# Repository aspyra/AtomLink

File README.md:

# AtomLink
 M5Stack Atom Lite based Bluetooth & infrared converter for use in Lego creations. Multiple software options to suit various needs.

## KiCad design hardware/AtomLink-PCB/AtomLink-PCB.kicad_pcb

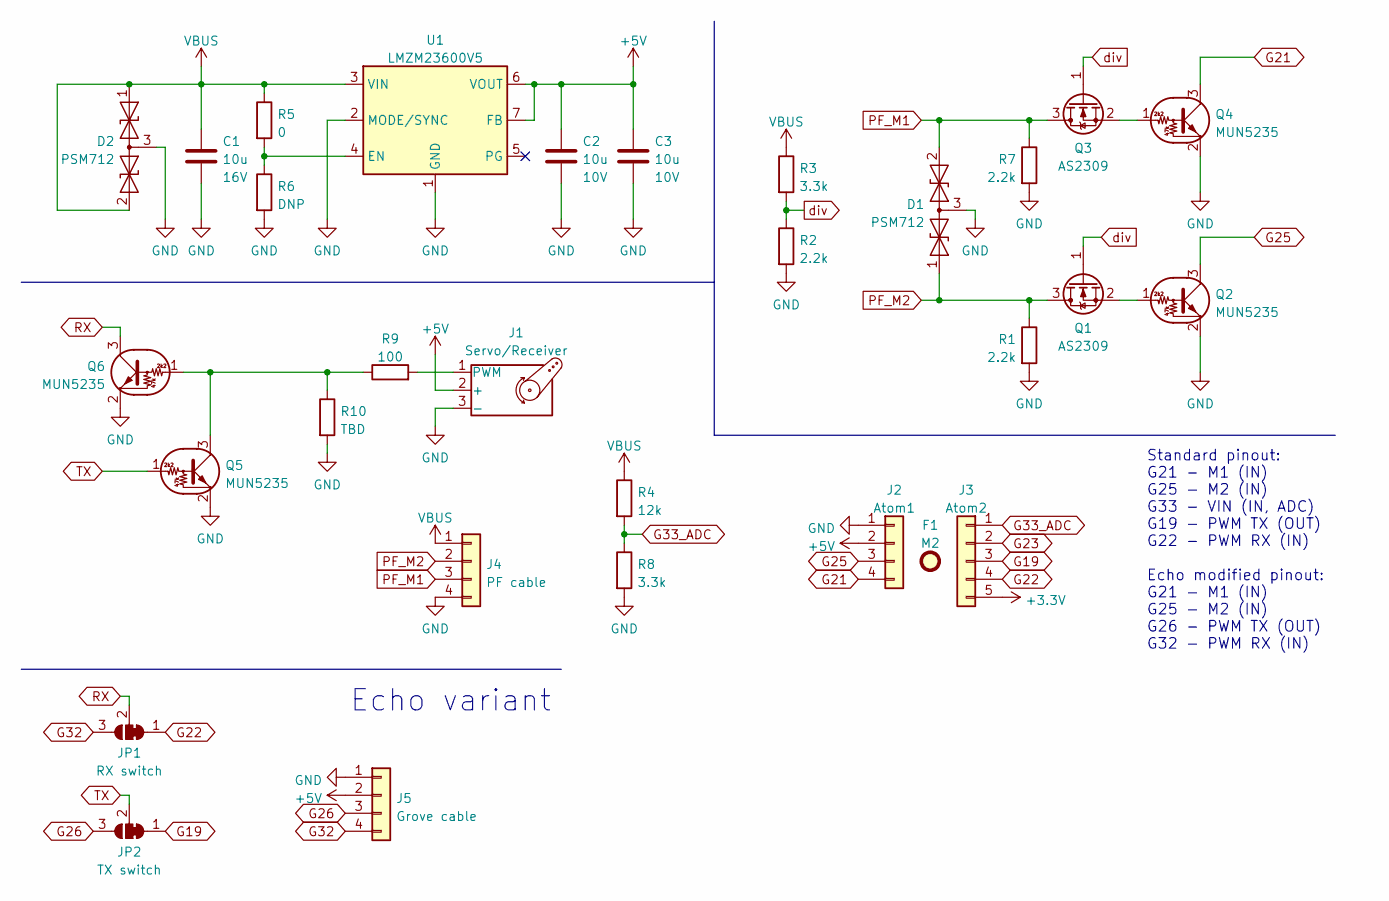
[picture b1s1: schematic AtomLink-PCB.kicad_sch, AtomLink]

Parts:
C1: 10u; C_1206_3216Metric; Rating 16V
C2, C3: 10u; C_0805_2012Metric; Rating 10V
D1, D2: PSM712; SOT-23
F1: M2; MountingHole_2.2mm_M2
J1: Servo/Receiver; PinHeader_1x03_P2.54mm_Horizontal
J2: Atom1; PinHeader_1x04_P2.54mm_Vertical
J3: Atom2; PinHeader_1x05_P2.54mm_Vertical
J4: PF cable; PinHeader_1x04_2mm
J5: Grove cable; PinHeader_1x04_2mm
JP1: RX switch; SolderJumper-3_P1.3mm_Bridged12_RoundedPad1.0x1.5mm
JP2: TX switch; SolderJumper-3_P1.3mm_Bridged12_RoundedPad1.0x1.5mm
Q1, Q3: AS2309; SOT-23
Q2, Q4, Q5, Q6: MUN5235; SOT-323_SC-70
R1, R7: 2.2k; R_0805_2012Metric
R2: 2.2k; R_0402_1005Metric
R3, R8: 3.3k; R_0402_1005Metric
R4: 12k; R_0402_1005Metric
R5: 0; R_0402_1005Metric
R6: DNP; R_0402_1005Metric
R9: 100; R_0402_1005Metric
R10: TBD; R_0402_1005Metric
U1: LMZM23600V5; Texas_SIL0010A_MicroSiP-10-1EP_3.8x3mm_P0.6mm_EP0.7x2.9mm_T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

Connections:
+3V3: J3.5
+5V: C2.1, C3.1, J1.2 (+), J2.2, J5.2, U1.6 (VOUT), U1.7 (FB)
G19: J3.3, JP2.1 (A)
G21: J2.4, Q4.3 (C)
G22: J3.4, JP1.1 (A)
G23: J3.2
G25: J2.3, Q2.3 (C)
G26: J5.3, JP2.3 (B)
G32: J5.4, JP1.3 (B)
G33_ADC: J3.1, R4.2, R8.1
GND: C1.2, C2.2, C3.2, D1.3 (common), D2.3 (common), J1.3 (-), J2.1, J4.4, J5.1, Q2.2 (E), Q4.2 (E), Q5.2 (E), Q6.2 (E), R1.2, R2.2, R6.2, R7.2, R8.2, R10.2, U1.1 (GND), U1.2 (MODE/SYNC), U1.11 (GND); also elsewhere on the board
unnamed: J1.1 (PWM), R9.2
unnamed: Q1.2 (S), Q2.1 (B)
unnamed: Q3.2 (S), Q4.1 (B)
unnamed: Q5.3 (C), Q6.1 (B), R9.1, R10.1
unnamed: R5.2, R6.1, U1.4 (EN)
PF_M1: D1.2 (A2), J4.3, Q3.3 (D), R7.1; also elsewhere on the board
PF_M2: D1.1 (A1), J4.2, Q1.3 (D), R1.1
RX: JP1.2 (C), Q6.3 (C)
TX: JP2.2 (C), Q5.1 (B)
VBUS: C1.1, D2.1 (A1), D2.2 (A2), J4.1, R3.1, R4.1, R5.1, U1.3 (VIN)
div: Q1.1 (G), Q3.1 (G), R2.1, R3.2

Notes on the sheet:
Echo variant
Standard pinout: G21 - M1 (IN) G25 - M2 (IN) G33 - VIN (IN, ADC) G19 - PWM TX (OUT) G22 - PWM RX (IN) Echo modified pinout: G21 - M1 (IN) G25 - M2 (IN) G26 - PWM TX (OUT) G32 - PWM RX (IN)

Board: 2 copper layers, 31 parts (23 on the bottom side), 20 nets, no tracks yet.

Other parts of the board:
R7#2: 2.2k; R_0805_2012Metric

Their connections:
GND: R7#2.2; also elsewhere on the board
PF_M1: R7#2.1; also elsewhere on the board

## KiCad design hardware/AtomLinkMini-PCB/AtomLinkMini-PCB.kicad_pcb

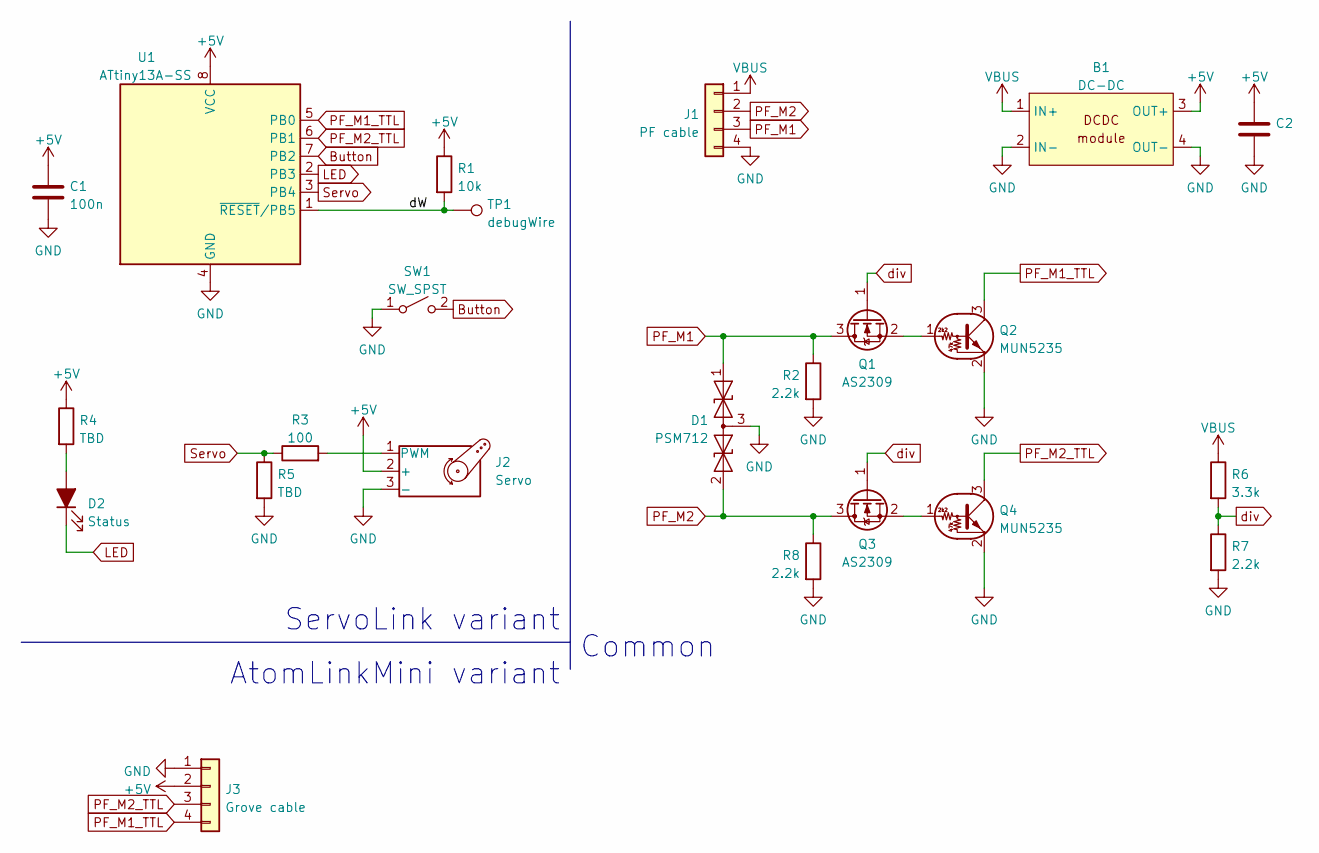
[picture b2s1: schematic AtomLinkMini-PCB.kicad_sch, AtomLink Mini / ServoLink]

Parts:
B1: DC-DC; DCDC-module
C1: 100n; C_0603_1608Metric_Pad1.08x0.95mm_HandSolder
C2: (no value)
D1: PSM712; SOT-23
D2: Status; LED_0603_1608Metric_Pad1.05x0.95mm_HandSolder
J1: PF cable; PinHeader_1x04_2mm
J2: Servo; PinHeader_1x03_P2.54mm_Vertical
J3: Grove cable; PinHeader_1x04_2mm
Q1, Q3: AS2309; SOT-23
Q2, Q4: MUN5235; SOT-323_SC-70
R1: 10k; R_0603_1608Metric_Pad0.98x0.95mm_HandSolder
R2, R8: 2.2k; R_0805_2012Metric_Pad1.20x1.40mm_HandSolder
R3: 100; R_0603_1608Metric_Pad0.98x0.95mm_HandSolder
R4, R5: TBD; R_0603_1608Metric_Pad0.98x0.95mm_HandSolder
R6: 3.3k; R_0603_1608Metric_Pad0.98x0.95mm_HandSolder
R7: 2.2k; R_0603_1608Metric_Pad0.98x0.95mm_HandSolder
SW1: SW_SPST; SW_Push_SPST_NO_Alps_SKRK
TP1: debugWire; PinHeader_1x01_P2.54mm_Vertical
U1: ATtiny13A-SS; SOIC-8_3.9x4.9mm_P1.27mm

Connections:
+5V: B1.3 (OUT+), C1.1, C2.1, J2.2 (+), J3.2, R1.1, R4.1, U1.8 (VCC)
/dW: R1.2, TP1.1, U1.1 (~RESET/PB5)
Button: SW1.2 (B), U1.7 (PB2)
GND: B1.2 (IN-), B1.4 (OUT-), C1.2, C2.2, D1.3 (common), J1.4, J2.3 (-), J3.1, Q2.2 (E), Q4.2 (E), R2.2, R5.2, R7.2, R8.2, SW1.1 (A), U1.4 (GND)
LED: D2.1 (K), U1.2 (PB3)
unnamed: D2.2 (A), R4.2
unnamed: J2.1 (PWM), R3.2
unnamed: Q1.2 (S), Q2.1 (B)
unnamed: Q3.2 (S), Q4.1 (B)
PF_M1: D1.1 (A1), J1.3, Q1.3 (D), R2.1
PF_M1_TTL: J3.4, Q2.3 (C), U1.5 (PB0)
PF_M2: D1.2 (A2), J1.2, Q3.3 (D), R8.1
PF_M2_TTL: J3.3, Q4.3 (C), U1.6 (PB1)
Servo: R3.1, R5.1, U1.3 (PB4)
VBUS: B1.1 (IN+), J1.1, R6.1
div: Q1.1 (G), Q3.1 (G), R6.2, R7.1

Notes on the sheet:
ServoLink variant
Common
AtomLinkMini variant

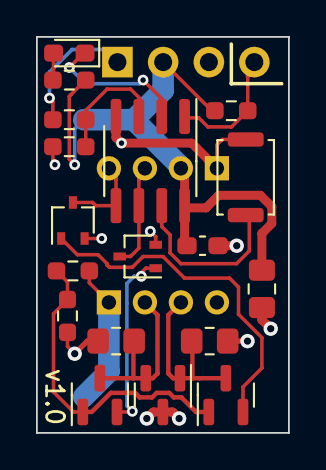
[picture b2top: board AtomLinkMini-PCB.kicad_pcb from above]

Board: 2 copper layers, 14.0 x 22.0 mm, 23 parts (1 on the bottom side), 16 nets.

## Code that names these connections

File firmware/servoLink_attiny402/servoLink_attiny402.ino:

#include <Servo_megaTinyCore.h>
/* AtomLink Mini v1.0 (Attiny402) pinout
 *  PF_M1 -> PA2/D3
 *  PF_M2 -> PA6/D0
 *  Servo -> PA3/D4
 *  Button-> PA7/D1
 *  LED   -> PA1/D2
 *  
  */
#define pin_LED 2
#define pin_BTN 1
#define pin_M1 3
#define pin_M2 0
#define pin_SRV 4

Servo srv;

int pos = 0;    // variable to store the servo position

void setup() {
  // initialize digital pin LED_BUILTIN as an output.
  pinMode(pin_BTN, INPUT_PULLUP);
  pinMode(pin_M1, INPUT_PULLUP);
  pinMode(pin_M2, INPUT_PULLUP);
  pinMode(pin_LED, OUTPUT);
  digitalWrite(pin_LED, HIGH);
  pinMode(pin_SRV, OUTPUT);
  digitalWrite(pin_SRV, LOW);
  srv.attach(pin_SRV);
}

// the loop function runs over and over again forever
void loop() {
  digitalWrite(pin_LED, digitalRead(pin_BTN));
  for (pos = 0; pos <= 180; pos += 1) { // goes from 0 degrees to 180 degrees
    // in steps of 1 degree
    srv.write(pos);              // tell servo to go to position in variable 'pos'
    delay(5);                       // waits 15ms for the servo to reach the position
  }
  for (pos = 180; pos >= 0; pos -= 1) { // goes from 180 degrees to 0 degrees
    srv.write(pos);              // tell servo to go to position in variable 'pos'
    delay(5);                       // waits 15ms for the servo to reach the position
  }
}

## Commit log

2023-06-15 Uploaded Atom Lite 3D model (step/f3d)
2023-06-16 Created PF reader circuit simulation
2023-06-16 Created KiCAD 6.0.4 project; started the schematic
2023-06-20 Schematic changes & layout started
2023-06-27 Schematic & layout changes
2023-06-27 Libraries created
2023-06-27 Added AtomLinkMini/ServoLink project (schematic, layout v1.0)
2023-06-27 Exported for PCBWay
2023-06-27 Added Echo variant
2024-02-14 Added atTiny13 schematic PDF, rewired schematic for atTiny402 & generated PDF
2024-02-14 Firmware started to test PCBA and MCU possibilities
